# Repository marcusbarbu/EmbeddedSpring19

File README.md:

# Embedded Project Spring 19

## What:
Detect falls using a pair of acceleromters and some decently jank code.

## Why:
Ultimately to get a good grade.
But also to work on directly interfacing with sensors without pre-rolled libraries.

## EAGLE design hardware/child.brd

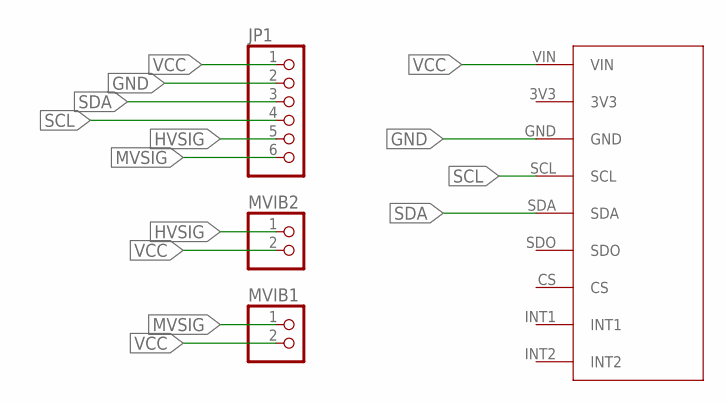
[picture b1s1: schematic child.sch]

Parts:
ACCEL: ADAFRUITADXL343
JP1: PINHD-1X6; 1X06
MVIB1, MVIB2: PINHD-1X2; 1X02

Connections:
GND: ACCEL.GND, JP1.2
HVSIG: JP1.5, MVIB2.1
MVSIG: JP1.6, MVIB1.1
SCL: ACCEL.SCL, JP1.4
SDA: ACCEL.SDA, JP1.3
VCC: ACCEL.VIN, JP1.1, MVIB1.2, MVIB2.2

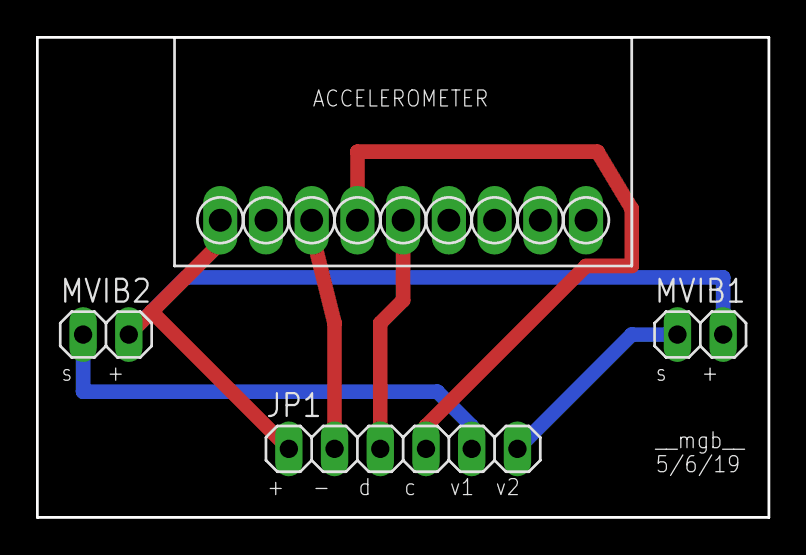
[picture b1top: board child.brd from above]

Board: 2 copper layers, 40.6 x 26.7 mm, 4 parts (0 on the bottom side), 6 nets.

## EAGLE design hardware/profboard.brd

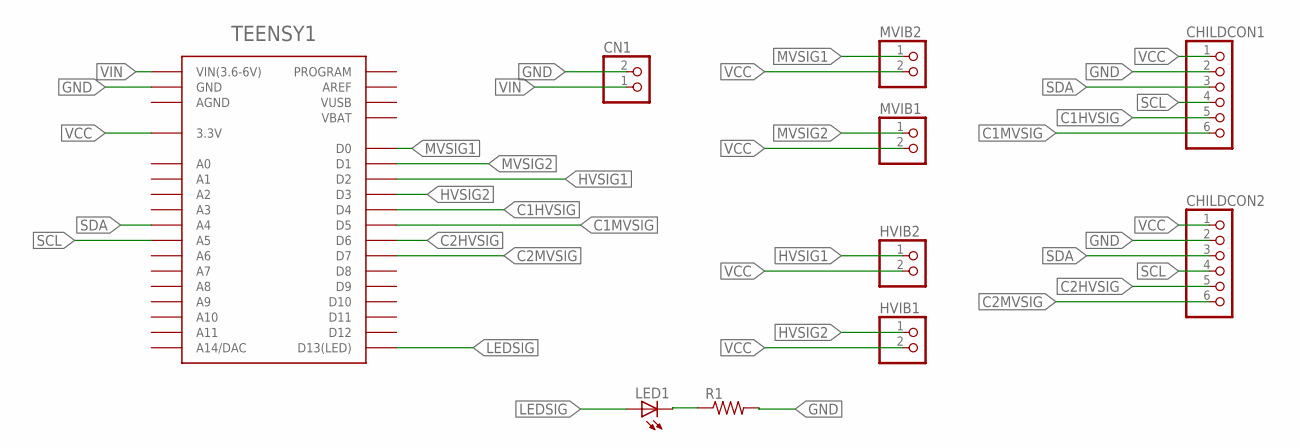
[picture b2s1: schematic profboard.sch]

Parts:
CHILDCON1, CHILDCON2: PINHD-1X6; 1X06
CN1: JST_2PIN-THM-RA; JST-PH-2-THM-RA
HVIB1, HVIB2: PINHD-1X2; 1X02
LED1: LED5MM
MVIB1, MVIB2: PINHD-1X2; 1X02
R1: R-US_0204/7; 0204/7
TEENSY1: TEENSY3.2

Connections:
C1HVSIG: CHILDCON1.5, TEENSY1.4 (D4)
C1MVSIG: CHILDCON1.6, TEENSY1.5 (D5)
C2HVSIG: CHILDCON2.5, TEENSY1.6 (D6)
C2MVSIG: CHILDCON2.6, TEENSY1.7 (D7)
GND: CHILDCON1.2, CHILDCON2.2, CN1.2 (1), R1.2, TEENSY1.G (GND), TEENSY1.GND
HVSIG1: HVIB2.1, TEENSY1.2 (D2)
HVSIG2: HVIB1.1, TEENSY1.3 (D3)
LEDSIG: LED1.A, TEENSY1.13 (D13(LED))
MVSIG1: MVIB2.1, TEENSY1.0 (D0)
MVSIG2: MVIB1.1, TEENSY1.1 (D1)
unnamed: LED1.K (C), R1.1
SCL: CHILDCON1.4, CHILDCON2.4, TEENSY1.19 (A5)
SDA: CHILDCON1.3, CHILDCON2.3, TEENSY1.18 (A4)
VCC: CHILDCON1.1, CHILDCON2.1, HVIB1.2, HVIB2.2, MVIB1.2, MVIB2.2, TEENSY1.3V (3.3V), TEENSY1.V (3.3V)
VIN: CN1.1 (2), TEENSY1.VIN (VIN(3.6-6V))

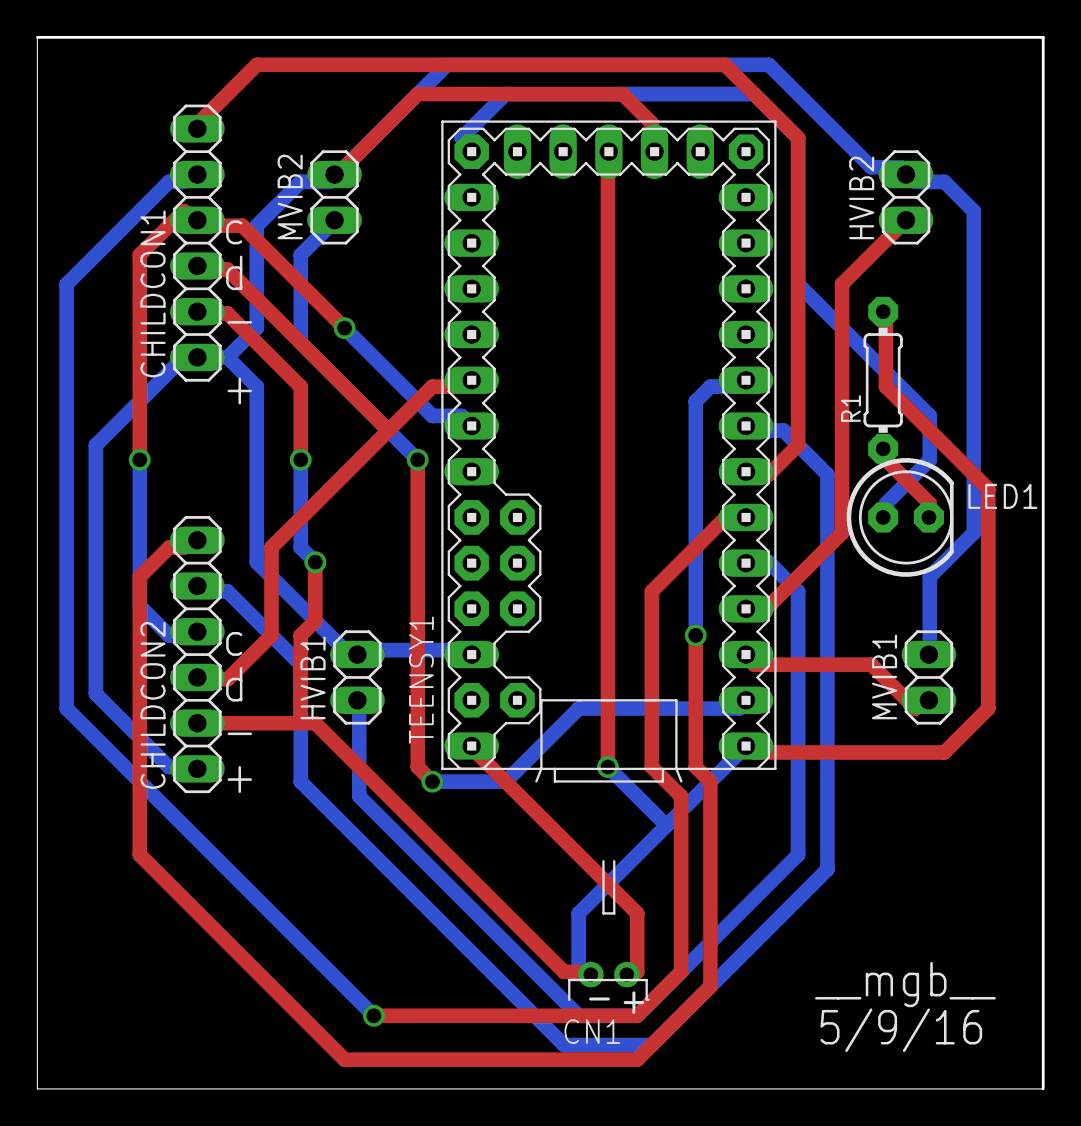
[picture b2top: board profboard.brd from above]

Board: 2 copper layers, 55.9 x 58.4 mm, 10 parts (0 on the bottom side), 15 nets.

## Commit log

2019-05-10 Initial commit (software only)
2019-05-10 added hardware
2019-05-11 preliminary detection attempted, doesn't really work at this point
2019-05-13 Realized I need to refactor a lot, so this is a savepoint.
2019-05-13 Something actually works, just needs refinement now
2019-05-16 Added STL files, working code
2019-05-16 changed || to &&
2019-09-03 Built out README for public release
